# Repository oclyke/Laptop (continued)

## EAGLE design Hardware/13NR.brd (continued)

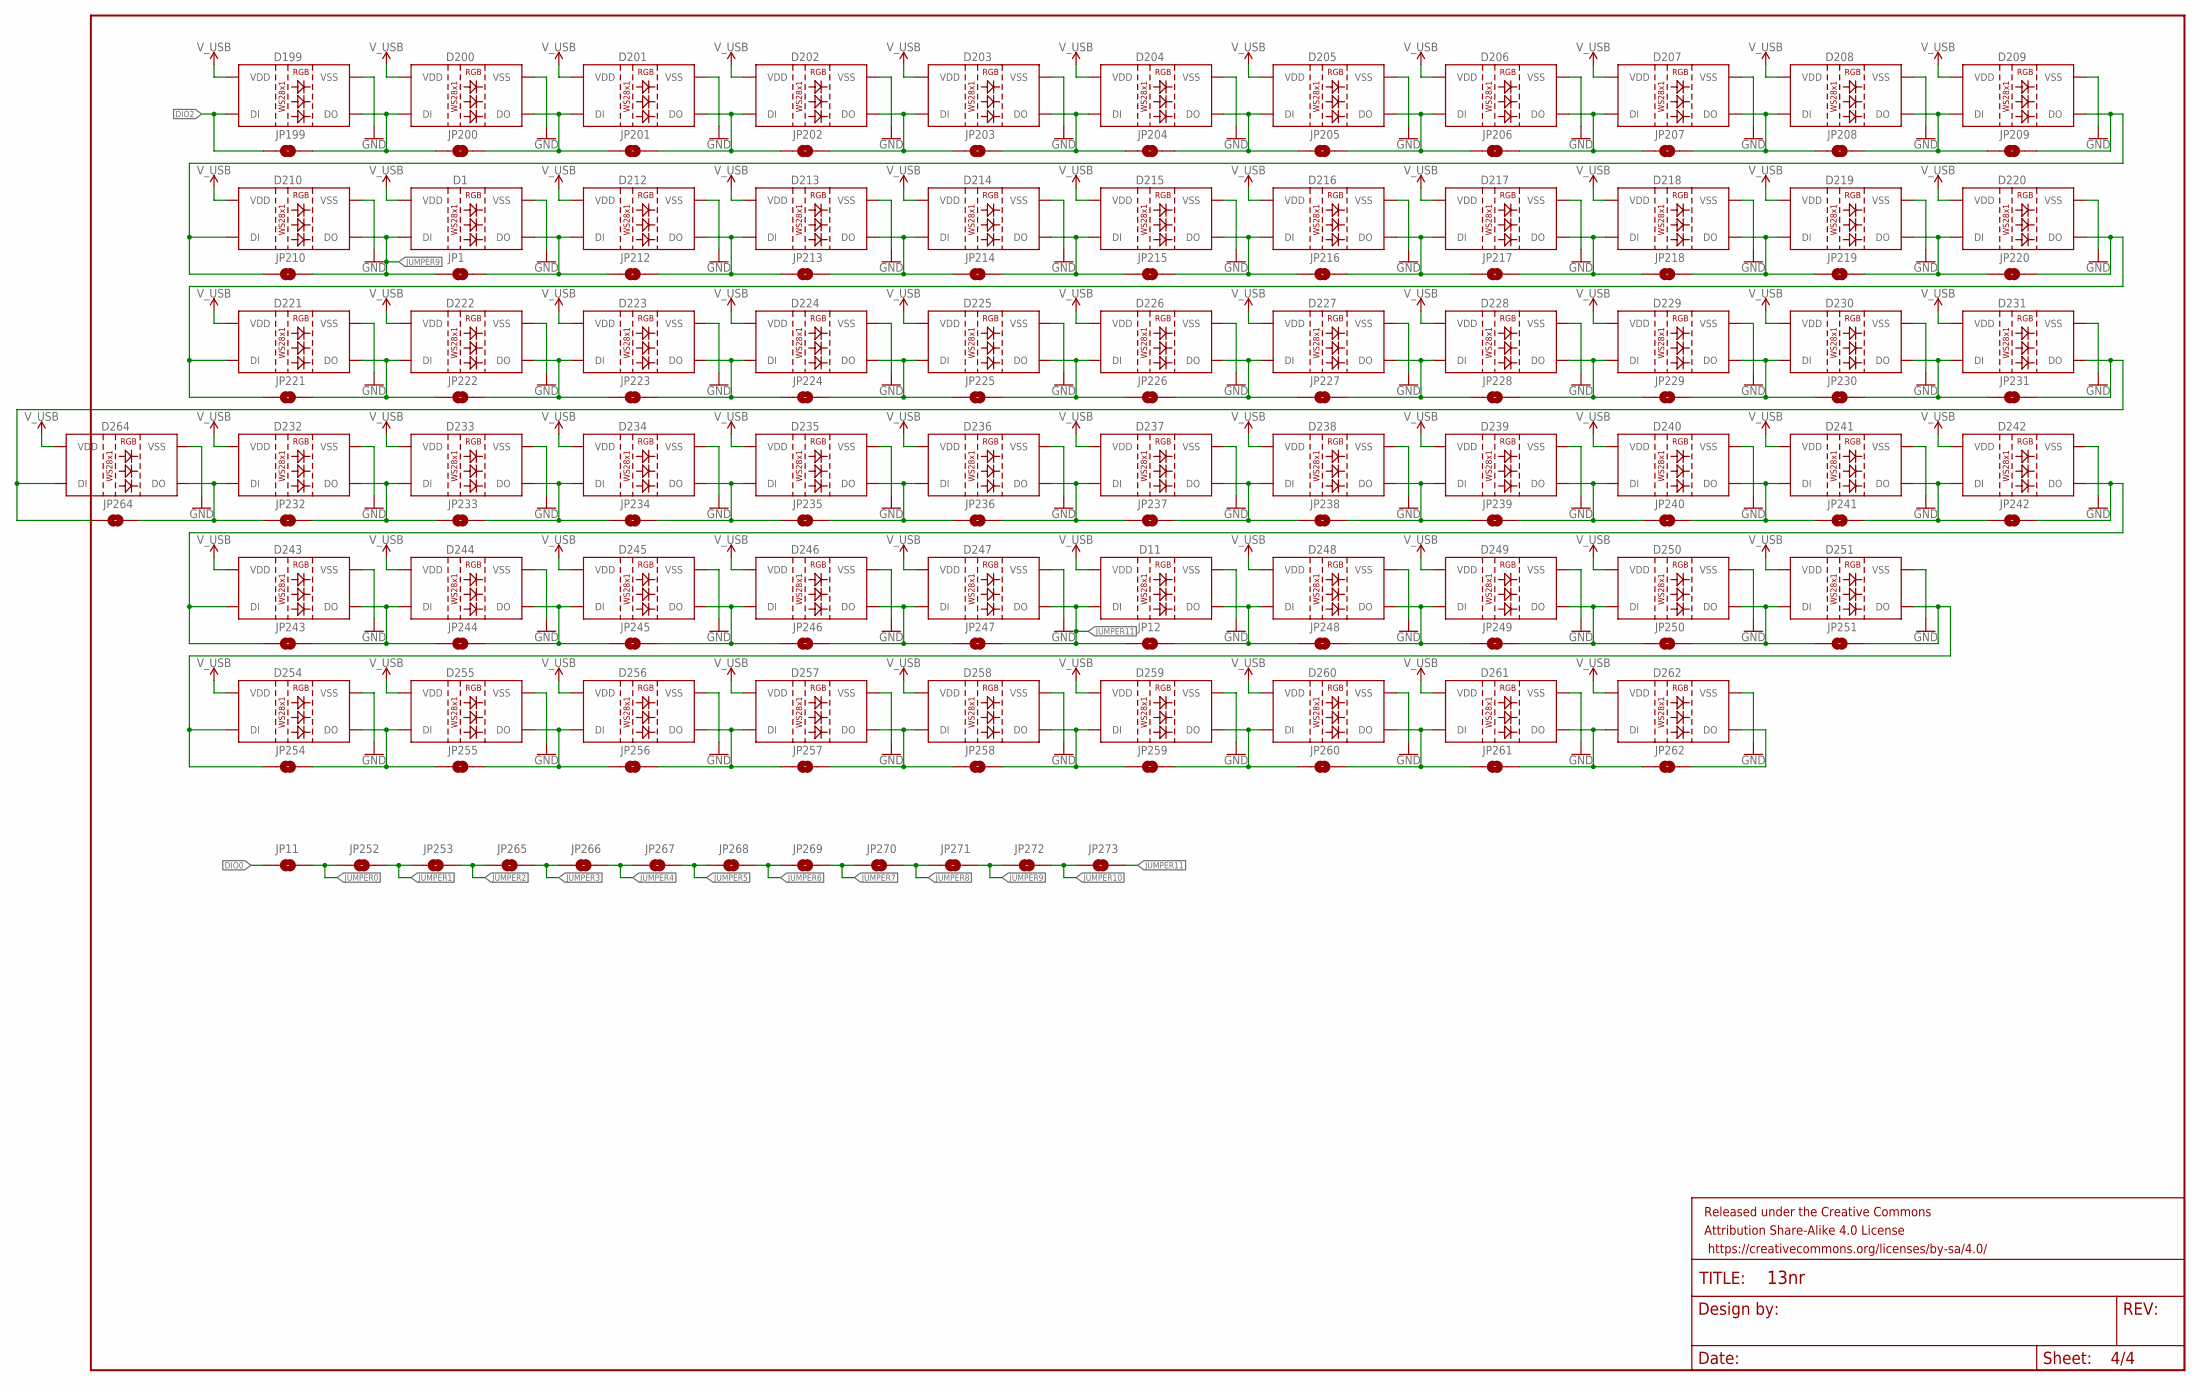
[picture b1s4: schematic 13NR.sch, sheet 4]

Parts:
D1, D11, D199, D200, D201, D202, D203, D204, D205, D206, D207, D208, D209, D210, D212, D213, D214, D215, D216, D217, D218, D219, D220, D221, D222, D223, D224, D225, D226, D227, D228, D229, D230, D231, D232, D233, D234, D235, D236, D237, D238, D239, D240, D241, D242, D243, D244, D245, D246, D247, D248, D249, D250, D251, D254, D255, D256, D257, D258, D259, D260, D261, D262, D264: WS2812B
FRAME4: FRAME-LEDGER; CREATIVE_COMMONS
JP1, JP11, JP12, JP199, JP200, JP201, JP202, JP203, JP204, JP205, JP206, JP207, JP208, JP209, JP210, JP212, JP213, JP214, JP215, JP216, JP217, JP218, JP219, JP220, JP221, JP222, JP223, JP224, JP225, JP226, JP227, JP228, JP229, JP230, JP231, JP232, JP233, JP234, JP235, JP236, JP237, JP238, JP239, JP240, JP241, JP242, JP243, JP244, JP245, JP246, JP247, JP248, JP249, JP250, JP251, JP252, JP253, JP254, JP255, JP256, JP257, JP258, JP259, JP260, JP261, JP262, JP264, JP265, JP266, JP267, JP268, JP269, JP270, JP271, JP272, JP273: JUMPER-SMT_2_NO_NO-SILK; SMT-JUMPER_2_NO_NO-SILK

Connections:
DIO0: JP11.1; also elsewhere on the board
DIO2: D199.4 (DI), JP199.1; also elsewhere on the board
DIO104: D209.2 (DO), D210.4 (DI), JP209.2, JP210.1
DIO105: D202.2 (DO), D203.4 (DI), JP202.2, JP203.1
DIO106: D204.2 (DO), D205.4 (DI), JP204.2, JP205.1
DIO107: D206.2 (DO), D207.4 (DI), JP206.2, JP207.1
DIO108: D208.2 (DO), D209.4 (DI), JP208.2, JP209.1
DIO110: D213.2 (DO), D214.4 (DI), JP213.2, JP214.1
DIO111: D215.2 (DO), D216.4 (DI), JP215.2, JP216.1
DIO112: D217.2 (DO), D218.4 (DI), JP217.2, JP218.1
DIO113: D219.2 (DO), D220.4 (DI), JP219.2, JP220.1
DIO114: D220.2 (DO), D221.4 (DI), JP220.2, JP221.1
DIO115: D222.2 (DO), D223.4 (DI), JP222.2, JP223.1
DIO116: D224.2 (DO), D225.4 (DI), JP224.2, JP225.1
DIO117: D226.2 (DO), D227.4 (DI), JP226.2, JP227.1
DIO118: D228.2 (DO), D229.4 (DI), JP228.2, JP229.1
DIO119: D230.2 (DO), D231.4 (DI), JP230.2, JP231.1
DIO122: D233.2 (DO), D234.4 (DI), JP233.2, JP234.1
DIO123: D235.2 (DO), D236.4 (DI), JP235.2, JP236.1
DIO124: D237.2 (DO), D238.4 (DI), JP237.2, JP238.1
DIO125: D239.2 (DO), D240.4 (DI), JP239.2, JP240.1
DIO126: D241.2 (DO), D242.4 (DI), JP241.2, JP242.1
DIO128: D242.2 (DO), D243.4 (DI), JP242.2, JP243.1
DIO129: D244.2 (DO), D245.4 (DI), JP244.2, JP245.1
DIO130: D246.2 (DO), D247.4 (DI), JP246.2, JP247.1
DIO131: D248.2 (DO), D249.4 (DI), JP248.2, JP249.1
DIO132: D250.2 (DO), D251.4 (DI), JP250.2, JP251.1
DIO134: D251.2 (DO), D254.4 (DI), JP251.2, JP254.1
DIO135: D255.2 (DO), D256.4 (DI), JP255.2, JP256.1
DIO136: D257.2 (DO), D258.4 (DI), JP257.2, JP258.1
DIO137: D259.2 (DO), D260.4 (DI), JP259.2, JP260.1
DIO138: D261.2 (DO), D262.4 (DI), JP261.2, JP262.1
GND: D1.3 (VSS), D11.3 (VSS), D199.3 (VSS), D200.3 (VSS), D201.3 (VSS), D202.3 (VSS), D203.3 (VSS), D204.3 (VSS), D205.3 (VSS), D206.3 (VSS), D207.3 (VSS), D208.3 (VSS), D209.3 (VSS), D210.3 (VSS), D212.3 (VSS), D213.3 (VSS), D214.3 (VSS), D215.3 (VSS), D216.3 (VSS), D217.3 (VSS), D218.3 (VSS), D219.3 (VSS), D220.3 (VSS), D221.3 (VSS), D222.3 (VSS), D223.3 (VSS), D224.3 (VSS), D225.3 (VSS), D226.3 (VSS), D227.3 (VSS), D228.3 (VSS), D229.3 (VSS), D230.3 (VSS), D231.3 (VSS), D232.3 (VSS), D233.3 (VSS), D234.3 (VSS), D235.3 (VSS), D236.3 (VSS), D237.3 (VSS), D238.3 (VSS), D239.3 (VSS), D240.3 (VSS), D241.3 (VSS), D242.3 (VSS), D243.3 (VSS), D244.3 (VSS), D245.3 (VSS), D246.3 (VSS), D247.3 (VSS), D248.3 (VSS), D249.3 (VSS), D250.3 (VSS), D251.3 (VSS), D254.3 (VSS), D255.3 (VSS), D256.3 (VSS), D257.3 (VSS), D258.3 (VSS), D259.3 (VSS), D260.3 (VSS), D261.3 (VSS), D262.3 (VSS), D264.3 (VSS); also elsewhere on the board
JUMPER0: JP11.2, JP252.1; also elsewhere on the board
JUMPER1: JP252.2, JP253.1; also elsewhere on the board
JUMPER2: JP253.2, JP265.1; also elsewhere on the board
JUMPER3: JP265.2, JP266.1; also elsewhere on the board
JUMPER4: JP266.2, JP267.1; also elsewhere on the board
JUMPER5: JP267.2, JP268.1; also elsewhere on the board
JUMPER6: JP268.2, JP269.1; also elsewhere on the board
JUMPER7: JP269.2, JP270.1; also elsewhere on the board
JUMPER8: JP270.2, JP271.1; also elsewhere on the board
JUMPER9: D1.4 (DI), D210.2 (DO), JP1.1, JP210.2, JP271.2, JP272.1
JUMPER10: D231.2 (DO), D264.4 (DI), JP231.2, JP264.1, JP272.2, JP273.1
JUMPER11: D11.4 (DI), D247.2 (DO), JP12.1, JP247.2, JP273.2
unnamed: D1.2 (DO), D212.4 (DI), JP1.2, JP212.1
unnamed: D199.2 (DO), D200.4 (DI), JP199.2, JP200.1
unnamed: D203.2 (DO), D204.4 (DI), JP203.2, JP204.1
unnamed: D201.2 (DO), D202.4 (DI), JP201.2, JP202.1
unnamed: D207.2 (DO), D208.4 (DI), JP207.2, JP208.1
unnamed: D205.2 (DO), D206.4 (DI), JP205.2, JP206.1
unnamed: D214.2 (DO), D215.4 (DI), JP214.2, JP215.1
unnamed: D212.2 (DO), D213.4 (DI), JP212.2, JP213.1
unnamed: D218.2 (DO), D219.4 (DI), JP218.2, JP219.1
unnamed: D216.2 (DO), D217.4 (DI), JP216.2, JP217.1
unnamed: D221.2 (DO), D222.4 (DI), JP221.2, JP222.1
unnamed: D225.2 (DO), D226.4 (DI), JP225.2, JP226.1
unnamed: D223.2 (DO), D224.4 (DI), JP223.2, JP224.1
unnamed: D229.2 (DO), D230.4 (DI), JP229.2, JP230.1
unnamed: D227.2 (DO), D228.4 (DI), JP227.2, JP228.1
unnamed: D232.2 (DO), D233.4 (DI), JP232.2, JP233.1
unnamed: D236.2 (DO), D237.4 (DI), JP236.2, JP237.1
unnamed: D234.2 (DO), D235.4 (DI), JP234.2, JP235.1
unnamed: D240.2 (DO), D241.4 (DI), JP240.2, JP241.1
unnamed: D238.2 (DO), D239.4 (DI), JP238.2, JP239.1
unnamed: D243.2 (DO), D244.4 (DI), JP243.2, JP244.1
unnamed: D11.2 (DO), D248.4 (DI), JP12.2, JP248.1
unnamed: D245.2 (DO), D246.4 (DI), JP245.2, JP246.1
unnamed: D249.2 (DO), D250.4 (DI), JP249.2, JP250.1
unnamed: D254.2 (DO), D255.4 (DI), JP254.2, JP255.1
unnamed: D258.2 (DO), D259.4 (DI), JP258.2, JP259.1
unnamed: D256.2 (DO), D257.4 (DI), JP256.2, JP257.1
unnamed: D262.2 (DO), JP262.2
unnamed: D260.2 (DO), D261.4 (DI), JP260.2, JP261.1
unnamed: D200.2 (DO), D201.4 (DI), JP200.2, JP201.1
unnamed: D232.4 (DI), D264.2 (DO), JP232.1, JP264.2
V_USB: D1.1 (VDD), D11.1 (VDD), D199.1 (VDD), D200.1 (VDD), D201.1 (VDD), D202.1 (VDD), D203.1 (VDD), D204.1 (VDD), D205.1 (VDD), D206.1 (VDD), D207.1 (VDD), D208.1 (VDD), D209.1 (VDD), D210.1 (VDD), D212.1 (VDD), D213.1 (VDD), D214.1 (VDD), D215.1 (VDD), D216.1 (VDD), D217.1 (VDD), D218.1 (VDD), D219.1 (VDD), D220.1 (VDD), D221.1 (VDD), D222.1 (VDD), D223.1 (VDD), D224.1 (VDD), D225.1 (VDD), D226.1 (VDD), D227.1 (VDD), D228.1 (VDD), D229.1 (VDD), D230.1 (VDD), D231.1 (VDD), D232.1 (VDD), D233.1 (VDD), D234.1 (VDD), D235.1 (VDD), D236.1 (VDD), D237.1 (VDD), D238.1 (VDD), D239.1 (VDD), D240.1 (VDD), D241.1 (VDD), D242.1 (VDD), D243.1 (VDD), D244.1 (VDD), D245.1 (VDD), D246.1 (VDD), D247.1 (VDD), D248.1 (VDD), D249.1 (VDD), D250.1 (VDD), D251.1 (VDD), D254.1 (VDD), D255.1 (VDD), D256.1 (VDD), D257.1 (VDD), D258.1 (VDD), D259.1 (VDD), D260.1 (VDD), D261.1 (VDD), D262.1 (VDD), D264.1 (VDD); also elsewhere on the board

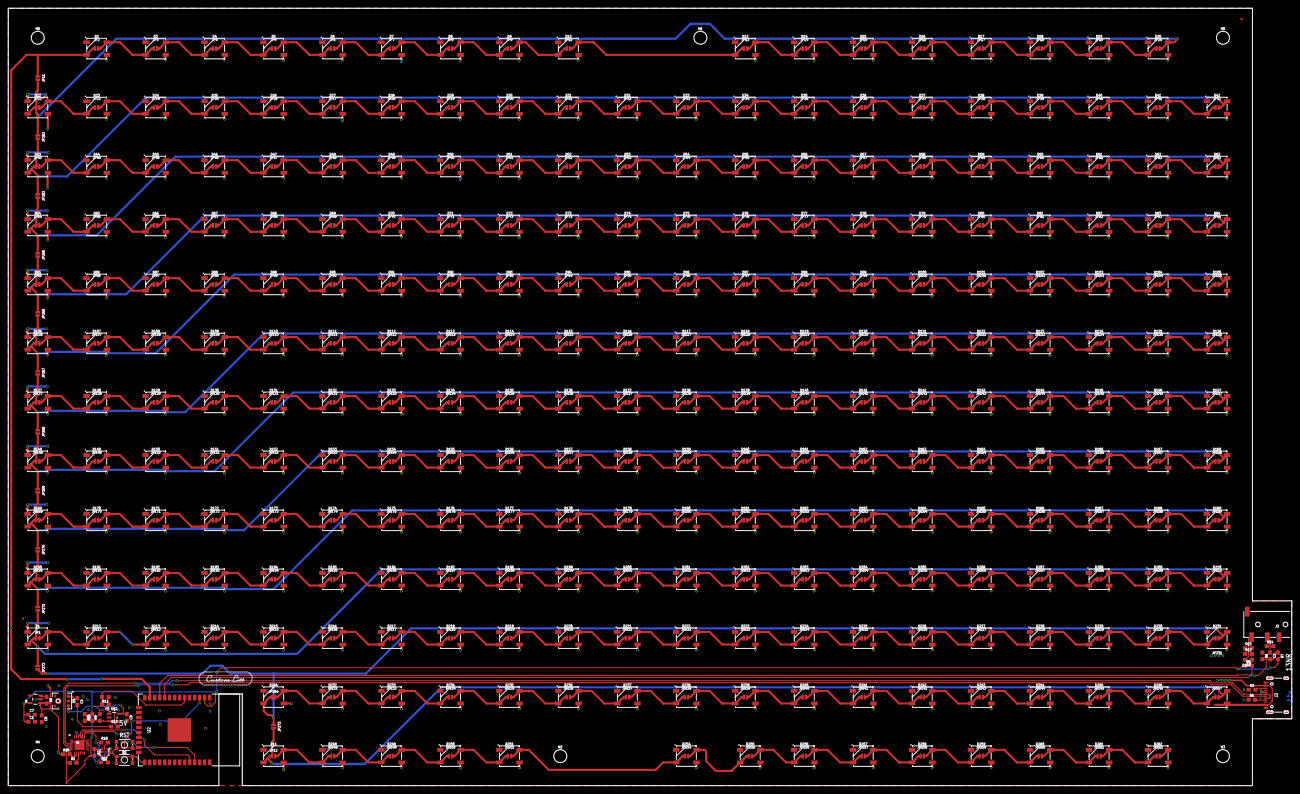
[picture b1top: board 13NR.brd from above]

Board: 2 copper layers, 326.5 x 197.8 mm, 579 parts (1 on the bottom side), 286 nets.

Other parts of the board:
U$1: UNNAMED#PNG
U$3: CEC7B2_1EE547F747C2467BB1A21A2065860725_MV2#JPG

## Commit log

2019-05-08 initial board layout
2019-07-08 updating mic and trrs circuits
2019-07-24 changing to 0603
2019-10-01 partially through layout
2019-10-02 updating layout, fixing bad commit
2019-10-04 completing initial 13 in layout, ready for design review with jason
2019-10-09 13 inch v01 laid out, ready to order
2019-10-17 updating 13NR, to move for mounting stuff
2019-10-18 moving power to other side
2019-10-22 strange gerber issue, counting a trace on dimension layer
2019-11-08 adding audio test
2019-11-20 most of barebones backedn finished
2019-12-16 updating firmware, fixing repo on computer
2019-12-17 adding artnet+audiosource changin
2019-12-17 fixing hard reset when pulling bad values fromEEPROMfor SSID/Password
2019-12-18 Artnet is functioning, needs a bit of tweaking to intelligently handle startUniverse/startaddress
2019-12-20 post-jason talk- mid phase 2
2019-12-21 switch to BLE interface for serial
    drop-in replacement for the old "BluetoothSerial.h"
    most commonly used functions are implemented, more could be added later if needed
    tested very well for typical length transmissions
    poor test setup may have caused/contributed to dropped characters after ~231 bytes, may need additional investigation
2019-12-28 reverting back to old firmware for a second
2019-12-28 adding in owens changes
2019-12-28 pushing up comments to bluetoothInterface
2020-01-01 updating a few patterns, adding in framedelay, frameskip
2020-01-02 temporary initartnet fix for when wifi not connected properly
2020-01-02 add CustomLitt uuid for filtering
2020-01-02 fix error when sending data out over bluetooth
    apparently it is important to start all the services even if they appear not to be used.
2020-01-03 adding in left/right for mic capability
2020-01-03 adding buffered out function, need to add headphone jack functionality
2020-01-03 adding license
2020-01-04 adding diagonal function beginning
2020-01-10 fixing artnet
2020-01-10 adding initialization for EEPROM, EEPROM properly handles wifi settings
2020-01-11 adding beginning of setting sender function
2020-01-13 adding setting sender, all patterns finished, adding diagonals
2020-02-05 adding deviceName, updating some functions like audio reaction and blending to not be state dependent
2020-02-05 starting to reroute 15 inch model
2020-02-07 routing 15 inch
2020-02-10 updating 13 inch, finish layout of 15 inch
2020-02-11 getting closer to final 15 inch layout
2020-02-27 final airwires on 13 inch retina, need to copy and move holes
2020-02-29 updating 15TB outer dimensions, still need to re-place holes
2020-03-03 updating 13NR
2020-03-11 getting 4 boards polished
2020-03-12 polishing 13tb and 13r
2020-03-16 final touches, polishing, jumpers, CAM on all boards
2020-06-23 use direct characteristic read/write control
2020-06-23 set IP address on connection
2020-06-23 replace command descriptions
2020-06-23 change access properties on command / read only characteristics
2020-06-23 add functions to easily initialize BLE parameters
2020-06-23 initialize most values
    the gradient needs more work
2020-06-26 change gradient control scheme
    this makes it so that the current gradient index can be specified
    when the index is specified the value of the gradient color characteristic is updated to match
    the gradient color can then be read
    this allows the controlling device to poll the gradient on its own time
2020-07-15 update EEPROM to use Preferences library
    Also includes fixes so that device name, ssid, and password are correctly communicated
2020-07-16 add network status characteristic
2020-07-16 change network status characteristic to RWN
    Read: indicate actual network status of device
    Write: request a change in network status
    (notifications occur when device changes network status)
2020-07-21 remove redundant network status set
2020-07-22 change network status request handling
2020-07-28 add recovery strapping pin
    temporary recovery option for #10
2020-10-16 pushing final board changes
2020-11-16 updating files
2021-01-09 fix strict warnings and add hardware configs
2021-01-22 saving these big changes
    but I need to step back and retain some more of Andy's audio code. I thought I could make it better but I just stripped out the creative genius
2021-01-22 restore andy's audio code + refactor audio sensitivity
2021-01-24 stuff
2021-02-02 fix 13NR board def
2021-02-02 replace speed ble ops
2021-02-03 remove custom color
    use color gradient 0th index as solid color
2021-02-03 gamma correction
2021-02-03 add 15TB board def
2021-02-03 add 15TB board def + fix 13NR def
2021-02-03 add speed control
2021-02-09 guard led access against out-of-bounds
    fixes a crash that could occur when leds[-1] was accessed
2021-02-09 break feedback loop of gamma correction
    gamma correction was recursively applied on every output loop which caused much faster dimming than desired
2021-02-09 decouple fft fade speed from animation loop speed
2021-02-09 remove temporary speed vars
    these are no longer used
2021-02-10 fix apparent direction of gradient in l/r u/d scroll modes
2021-02-10 fix ultra fast fade in audio buffer modes
2021-02-10 slow down fade + flicker
2021-02-16 simplify fftAvg()
    we were experiencing crashes associated with this function
